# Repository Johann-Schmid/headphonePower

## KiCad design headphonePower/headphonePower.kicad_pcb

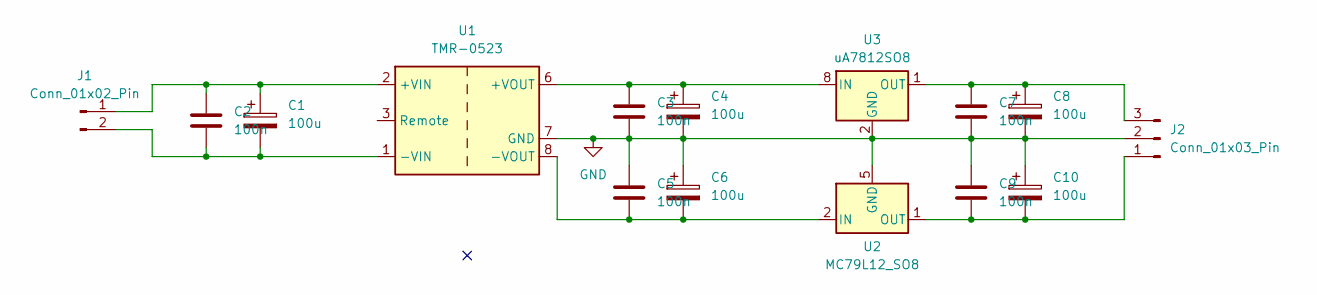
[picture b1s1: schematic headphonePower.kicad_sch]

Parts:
C1, C4, C6, C8, C10: 100u; CP_Radial_D6.3mm_P2.50mm
C2, C3, C5, C7, C9: 100n; C_1206_3216Metric
J1: Conn_01x02_Pin; PinHeader_1x02_P2.54mm_Vertical
J2: Conn_01x03_Pin; PinHeader_1x03_P2.54mm_Vertical
U1: TMR-0523; Converter_DCDC_TRACO_TMR-xxxx_THT
U2: MC79L12_SO8; SOIC-8_3.9x4.9mm_P1.27mm
U3: uA7812SO8; SO-8_3.9x4.9mm_P1.27mm

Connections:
GND: C3.2, C4.2, C5.1, C6.1, C7.2, C8.2, C9.1, C10.1, J2.2, U1.7 (GND), U2.5 (GND), U3.2 (GND)
unnamed: C1.1, C2.1, J1.1, U1.2 (+VIN)
unnamed: C1.2, C2.2, J1.2, U1.1 (-VIN)
unnamed: C9.2, C10.2, J2.1, U2.1 (OUT)
unnamed: C7.1, C8.1, J2.3, U3.1 (OUT)
unnamed: C3.1, C4.1, U1.6 (+VOUT), U3.8 (IN)
unnamed: C5.2, C6.2, U1.8 (-VOUT), U2.2 (IN), U2.3 (IN), U2.6 (IN), U2.7 (IN)

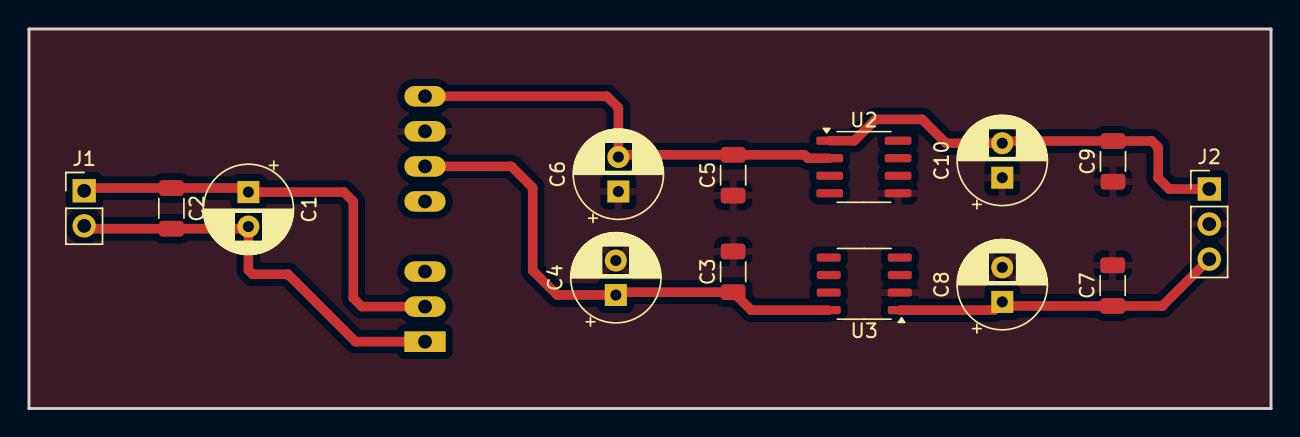
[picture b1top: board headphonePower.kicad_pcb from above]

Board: 2 copper layers, 90.0 x 27.5 mm, 15 parts (1 on the bottom side), 7 nets.

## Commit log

2024-03-12 pcb
    pcb
